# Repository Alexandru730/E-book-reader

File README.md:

# 📦 ESP32-C6 ePaper Project

Un proiect hardware ce integreaza un modul **ESP32-C6**, un **display e-Paper 7.5"**, alimentare prin **baterie Li-Ion** si conexiuni de testare prin **testpad-uri**. 

---

## 📊 Diagrama bloc

---

## 📦 BOM – Bill of Materials
| Componenta                 | Achizitie                                     | Datasheet                                   |
|---------------------------|-----------------------------------------------|---------------------------------------------|
| PFMF.050.1                | [Cumpara](https://ro.mouser.com/ProductDetail/Schurter/PFMF.050.2?qs=1auRipcfynCums5v1iucSA%3D%3D)                     | [Datasheet](https://ro.mouser.com/datasheet/2/358/typ_PFMF-1275918.pdf)                 |
| USB4110-GF-A              | [Cumpara](https://ro.mouser.com/ProductDetail/GCT/USB4110-GF-A?qs=KUoIvG%2F9IlYiZvIXQjyJeA%3D%3D)                     | [Datasheet](https://ro.mouser.com/datasheet/2/837/GCT_USB4110_Product_Drawing___20k_cycles-3455479.pdf)                 |
| USBLC6-2SC6Y              | [Cumpara](https://ro.mouser.com/ProductDetail/STMicroelectronics/USBLC6-2SC6Y?qs=gNDSiZmRJS%2FOgDexvXkdow%3D%3D)                     | [Datasheet](https://ro.mouser.com/datasheet/2/389/usblc6_2sc6y-1852505.pdf)                 |
| SD0805S020S1R0            | [Cumpara](https://ro.mouser.com/ProductDetail/KYOCERA-AVX/SD0805S020S1R0?qs=jCA%252BPfw4LHbpkAoSnwrdjw%3D%3D)                     | [Datasheet](https://ro.mouser.com/datasheet/2/40/schottky-3165252.pdf)                 |
| DMG2305UX-7               | [Cumpara](https://ro.mouser.com/ProductDetail/Diodes-Incorporated/DMG2305UX-7?qs=L1DZKBg7t5F%2FNBHrjfxC%252Bg%3D%3D)                     | [Datasheet](https://www.diodes.com/assets/Datasheets/DMG2305UX.pdf)                 |
| XC6220A331MR-G            | [Cumpara](https://ro.mouser.com/ProductDetail/Torex-Semiconductor/XC6220A331MR-G?qs=AsjdqWjXhJ8ZSWznL1J0gg%3D%3D)                     | [Datasheet](https://ro.mouser.com/datasheet/2/760/xc6220-3371556.pdf)                 |
| Condensator 100 uF TANT   | [Cumpara](https://ro.mouser.com/ProductDetail/KYOCERA-AVX/TAJW107M010RNJ?qs=Wtp%252Bf%2FAeVqIH8v1VxV%252B1Rg%3D%3D)                     | [Datasheet](https://ro.mouser.com/datasheet/2/40/TAJ-3165264.pdf)                 |
| 112A-TAAR-R03_ATTEND      | [Cumpara](https://www.digikey.ro/en/products/detail/attend-technology/112A-TAAR-R03/17633923)                     | [Datasheet](https://www.attend.com.tw/data/download/file/112A-TAAR-R03_Spec.pdf)                 |
| ESP32-C6-WROOM-1-N8       | [Cumpara](https://ro.mouser.com/ProductDetail/Espressif-Systems/ESP32-C6-WROOM-1-N8?qs=8Wlm6%252BaMh8ST02Gmwp74cw%3D%3D)                     | [Datasheet](https://ro.mouser.com/datasheet/2/891/Espressif_ESP32_C6_WROOM_1__Datasheet_V0_1_PRELIMI-3239987.pdf)                 |
| MCP73831                  | [Cumpara](https://ro.mouser.com/ProductDetail/Microchip-Technology/MCP73831T-2ACI-OT?qs=yUQqVecv4qvbBQBGbHx0Mw%3D%3D)                     | [Datasheet](https://ro.mouser.com/datasheet/2/268/MCP73831_Family_Data_Sheet_DS20001984H-3441711.pdf)                 |
| CHG_LED                   | [Cumpara](https://store.comet.srl.ro/Catalogue/Product/40478/)                     | [Datasheet](https://www.snapeda.com/parts/KP-1608SURCK/Kingbright/datasheet/)                 |
| SI1308EDL-T1-GE3          | [Cumpara](https://ro.mouser.com/ProductDetail/Vishay-Semiconductors/SI1308EDL-T1-GE3?qs=bX1%252BNvsK%2FBramh9tgpOaEw%3D%3D)                     | [Datasheet](https://www.vishay.com/doc?63399)                 |
| MBR0530                   | [Cumpara](https://ro.mouser.com/ProductDetail/Micro-Commercial-Components-MCC/MBR0530-T?qs=9VyI4qLX4NTSXkb9ynzJnA%3D%3D)                     | [Datasheet](https://ro.mouser.com/datasheet/2/258/mcc_mbr0520~mbr0560sod123-1179695.pdf)                 |
| Bobina                    | [Cumpara](https://ro.mouser.com/ProductDetail/Wurth-Elektronik/744043680?qs=PGXP4M47uW6VkZq%252BkzjrHA%3D%3D)                     | [Datasheet](https://www.we-online.com/components/products/datasheet/744043680.pdf)                 |
| FH34SRJ-24S-0.5SH_99_     | [Cumpara](https://ro.mouser.com/ProductDetail/Hirose-Connector/FH34SRJ-24S-0.5SH99?qs=vcbW%252B4%252BSTIpKBl5ap9J8Fw%3D%3D)                     | [Datasheet](https://ro.mouser.com/datasheet/2/185/FH34SRJ_24S_0_5SH_99__CL0580_1255_6_99_2DDrawing_0-1615044.pdf)                 |
| BME688                    | [Cumpara](https://ro.mouser.com/ProductDetail/Bosch-Sensortec/BME688?qs=IS%252B4QmGtzzqQoVDscqwx3A%3D%3D)                     | [Datasheet](https://ro.mouser.com/datasheet/2/783/bst_bme688_fl000-2307034.pdf)                 |
| BD5229G-TR                | [Cumpara](https://ro.mouser.com/ProductDetail/ROHM-Semiconductor/BD5229G-TR?qs=4kLU8WoGk0vvnhrrYwdszw%3D%3D)                     | [Datasheet](https://fscdn.rohm.com/en/products/databook/datasheet/ic/power/voltage_detector/bd52xxg-e.pdf)                 |
| Switch             | [Cumpara](https://ro.mouser.com/ProductDetail/CK/KMR221GULCLFS?qs=u2NJ%252B70r0goBXaNk7IrU0Q%3D%3D)                     | [Datasheet](https://www.ckswitches.com/media/1479/kmr2.pdf)                 |
| MAX17048G+T10             | [Cumpara](https://ro.mouser.com/ProductDetail/Analog-Devices-Maxim-Integrated/MAX17048G%2bT10?qs=D7PJwyCwLAoGnnn8jEPRBQ%3D%3D)                     | [Datasheet](https://ro.mouser.com/datasheet/2/609/MAX17048_MAX17049-3469099.pdf)                 |
| W25Q512JVEIQ              | [Cumpara](https://ro.mouser.com/ProductDetail/Winbond/W25Q512JVEIQ?qs=l7cgNqFNU1jw6svr3at6tA%3D%3D)                     | [Datasheet](https://ro.mouser.com/datasheet/2/949/Winbond_W25Q512JV_Datasheet-3240039.pdf)                 |
| PGB1010603MR              | [Cumpara](https://ro.mouser.com/ProductDetail/Littelfuse/PGB1010603MRHF?qs=KvZd0dN2Zg%2FuIq6icj%252BGKA%3D%3D)                     | [Datasheet](https://www.littelfuse.com/media?resourcetype=datasheets&itemid=8a337998-d54d-466b-be4e-dc5bcd1f9321&filename=littelfuse_pulseguard_pgb1_datasheet.pdf)                 |
| QWIIC_RIGHT_ANGLE         | [Cumpara](https://ro.mouser.com/ProductDetail/Analog-Devices-Maxim-Integrated/DS3231SN?qs=ffX8NcjNb2RmKAb9wAk9Ug%3D%3D)                    | [Datasheet](https://ro.mouser.com/datasheet/2/837/GCT_USB4110_Product_Drawing___20k_cycles-3455479.pdf)                 |
| DS3231SN#                 | [Cumpara](https://ro.mouser.com/ProductDetail/Analog-Devices-Maxim-Integrated/DS3231SN?qs=ffX8NcjNb2RmKAb9wAk9Ug%3D%3D)                     | [Datasheet](https://ro.mouser.com/datasheet/2/609/DS3231-3421123.pdf)                 |
| CPH3225A C10_SUPERCAP     | [Cumpara](https://ro.mouser.com/ProductDetail/Seiko-Semiconductors/CPH3225A?qs=3etwrb1wR%252BhUOph6lAO7eg%3D%3D)                     | [Datasheet](https://ro.mouser.com/datasheet/2/360/Seiko_Instruments_MicroBattery_E_20230330_2024Jan_-3561061.pdf)                 |
| Condensator 100nF         | [Cumpara](https://ro.mouser.com/ProductDetail/KYOCERA-AVX/06033G104ZAT2A?qs=NXubJDmysXJMPmHfVo6Z%252BA%3D%3D)                     | [Datasheet](https://ro.mouser.com/datasheet/2/40/KGM_Y5V-3223189.pdf)                 |
| Condensator 4.7uF         | [Cumpara](https://ro.mouser.com/ProductDetail/KYOCERA-AVX/0402ZD475MAT2A?qs=NBFAU1oqP4W4U2PCPHI0sg%3D%3D)                     | [Datasheet](https://ro.mouser.com/datasheet/2/40/cx5r_KGM-3223198.pdf)                 |
| Condensator 10uF          | [Cumpara](https://ro.mouser.com/ProductDetail/Samsung-Electro-Mechanics/CL10A106KQ8NNNL?qs=xZ%2FP%252Ba9zWqaes9JKSsob2Q%3D%3D)                     | [Datasheet](https://ro.mouser.com/datasheet/2/585/MLCC-1837944.pdf)                 |
| Condensator 1uF/50V       | [Cumpara](https://ro.mouser.com/ProductDetail/KYOCERA-AVX/06035D105MAT2A?qs=k4kUdCzLgS5%252BURKe1SOIeQ%3D%3D)                     | [Datasheet](https://ro.mouser.com/datasheet/2/40/cx5r_KGM-3223198.pdf)                 |
| Rezistenta 10K            | [Cumpara](https://ro.mouser.com/ProductDetail/Vishay-Beyschlag/MCS0402MD1002BE000?qs=17u8i%2FzlE8%2F9BrAaXkMk1w%3D%3D)                     | [Datasheet](https://www.vishay.com/doc?28952)                 |
| Rezistenta 200            | [Cumpara](https://ro.mouser.com/ProductDetail/Vishay-Beyschlag/MCS0402MD2000BE100?qs=3SvaY9RawMJNVte4F12%252BZQ%3D%3D)                     | [Datasheet](https://www.vishay.com/doc?28952)                 |
| Rezistenta 100K           | [Cumpara](https://ro.mouser.com/ProductDetail/Vishay-Beyschlag/MCT0603PD1003DP500?qs=5aG0NVq1C4wWAn8Ei3OpZA%3D%3D)                     | [Datasheet](https://www.vishay.com/doc?28916)                 |
| Rezistenta 2.2            | [Cumpara](https://ro.mouser.com/ProductDetail/SEI-Stackpole/RMCF0402FT2R20?qs=IPgv5n7u5QbBgyl0jwhwsA%3D%3D)                     | [Datasheet](https://ro.mouser.com/datasheet/2/385/SEI_RMCF_RMCP-3077565.pdf)                 |
| Rezistenta 5K1            | [Cumpara](https://www.venkel.com/part/TFCR0603-16W-K-5690FT)                     | [Datasheet](https://ro.mouser.com/datasheet/2/385/SEI_RMCF_RMCP-3077565.pdf)                 |
| Rezistenta 2K             | [Cumpara](https://ro.mouser.com/ProductDetail/Vishay-Beyschlag/MCS04020C2001FE000?qs=wTZ%2FFzl837YG0wIkZJJOwQ%3D%3D)                     | [Datasheet](https://www.vishay.com/doc?28705)                 |
| Rezistenta 0.47           | [Cumpara](https://ro.mouser.com/ProductDetail/SEI-Stackpole/CSR0402JKR470?qs=IPgv5n7u5QawIB6nBEt8wA%3D%3D)                     | [Datasheet](https://ro.mouser.com/datasheet/2/385/SEI_CSR_CSRN-3077593.pdf)                 |
| Rezistenta 15             | [Cumpara](https://ro.mouser.com/ProductDetail/YAGEO/RT0402FRE0715RL?qs=BXCcY9r%252B08DFFpLSkPOIqQ%3D%3D)                     | [Datasheet](https://ro.mouser.com/datasheet/2/447/PYu_RT_1_to_0_01_RoHS_L_15-3461507.pdf)                 |
                                                  |

---

## ⚙️ Functionalitate Hardware

- 🧠 **ESP32-C6**: procesor principal, WiFi si BLE
- 🖼️ **Display e-Paper 7.5”**: conectat prin interfata SPI
- 🔋 **Baterie Li-Ion 3.7V**: conectare directa la testpad-uri
- 🧪 **Testpad-uri**: pentru alimentare, masuratori si debugging
- 🧲 Toate GND-urile sunt conectate intr-un plan de masa dublu (top/bottom) cu **via stitching**

---

# Tabel Pini ESP32-C6 - Configuratie si Functii

| Nume            | GPIO / Pin       | Functie                              | Descriere                                                                 |
|-----------------|------------------|--------------------------------------|---------------------------------------------------------------------------|
| 3V3             | 3V3              | Sursa 3.3V                           | Asigura alimentarea necesara functionarii ESP32-C6 si componentelor logice |
| EN (Reset)      | EN               | Activare/Dezactivare microcontroler | Reset hardware prin semnal LOW                                            |
| USB_D-          | IO12             | Linie USB negativa                   | Parte din perechea diferentiala pentru USB 2.0                            |
| USB_D+          | IO13             | Linie USB pozitiva                   | Parte din perechea diferentiala pentru USB 2.0                            |
| Buton Boot      | IO9              | Mod bootloader                       | Se conecteaza la GND pentru a initia programarea                          |
| Buton Change    | IO15             | Mod operare                          | Comuta intre moduri definite in firmware                                  |
| TX (UART)       | GPIO16 (TXD0)    | UART TX                              | Transmitere date seriale                                                  |
| RX (UART)       | GPIO17 (RXD0)    | UART RX                              | Receptie date seriale                                                     |
| SCK (SPI)       | IO6              | SPI Clock                            | Ceas pentru comunicatia SPI                                               |
| MOSI (SPI)      | IO7              | SPI Master Out                       | Transmitere date SPI                                                      |
| MISO (SPI)      | IO2              | SPI Master In                        | Receptie date SPI                                                         |
| FLASH_CS        | IO11             | Chip Select NOR Flash                | Activeaza memoria flash                                                   |
| EPD_CS          | IO10             | Chip Select E-Paper                  | Activeaza ecranul E-Paper                                                 |
| EPD_DC          | IO5              | Comanda/Date E-Paper                 | Diferentiaza comenzi vs date pentru E-Paper                              |
| EPD_RST         | IO23             | Reset E-Paper                        | Reset hardware pentru E-Paper                                             |
| EPD_BUSY        | IO3              | Busy E-Paper                         | Semnalizeaza ca E-Paper este ocupat                                      |
| SDA (I2C)       | IO21             | I2C Data                             | Comunicatie cu RTC, BME688, etc.                                          |
| SCL (I2C)       | IO22             | I2C Clock                            | Ceas I2C                                                                  |
| SS_SD           | IO4              | Chip Select SD Card                  | Activeaza cardul SD                                                       |
| I2C_PW          | IO19             | Power control senzori I2C            | Activeaza/dezactiveaza alimentarea senzorilor I2C                         |
| EPD_3V3_C       | IO20             | Alimentare 3.3V E-Paper              | Sursa dedicata pentru E-Paper                                             |
| 32KHZ           | IO1              | Semnal 32kHz                         | Clock pentru RTC sau alte functii                                         |
| INT_RTC         | IO0              | Intrerupere RTC                      | Trezeste sistemul sau semnaleaza un eveniment RTC                         |
| RTC_RST         | IO18             | Reset RTC                            | Permite resetarea manuala a ceasului RTC                                  |

---

## 🖼️ Design Mecanic & 3D

- ✅ PCB proiectat si exportat 3D in Autodesk Fusion
- ✅ Model 3D complet pentru **baterie** si **display**, pe baza dimensiunilor din datasheet
- ✅ Integrare completa in **carcasa 3D** (asamblare in Fusion)
- ✅ Exploded view pentru randare si prezentare

---

## 🖼️ Randari

- ✅  
- ✅ 
- ✅ 

---
# Vizualizare 3D Autodesk

Model 3D interactiv găzduit pe Autodesk Viewer.

[🔗 Modelul direct in Autodesk Viewer](https://stud33517.autodesk360.com/shares/public/SH30dd5QT870c25f12fc75d2ac08da186a19).1

## Etape de implementare:
 - Am inceput cu asamblarea pieselor in schematic din biblioteca data, apoi cu trecerea la placa pcb, decuparea placii, masuratori luate pentru amplasarea corecta a pieselor si pentru integrarea usoara a placii in carcasa data.
 - A urmat amplasarea pieselor, am facut traseele de putere manual cu grosimea de 0.3mm, iar apoi pentru celelate trasee am folosit autoroute, cu grosimea de 0.16mm, un singur vias pe un traseu de putere am avut pentru ca nu am mai avut cum sa il leg pe layer-ul top.
 - Am facut planul de masa pe bottom si pe top, am folosit via stitching.
 - Iar apoi am trecut la pcb in 3d, am incarcat toate piesele in 3d si am trecut la masuratorile pentru baterie si ecran.
 - Bateria am facut-o simpla cu doua iesiri legate la doua testpaduri, vbat si gnd.
 - Display-ul l-am realizat dupa masuratorile date din datasheet, i-am facut si acel conector care intra in spatiul liber din placuta la connector display

# Erori
1. Am avut doua erori pe care le-am aprobat in pcb("Copper Width"), dar ele aveau grosimea buna.
2. Am gresit ceva si m-am intors la o varianta anterioara a pcb ului si dupa nu a mai fost sincronizat cu schematicul si nu mi-a mai mers randarea in 3d a placii si am luat totul de la inceput.
3. Mi s-a sters o componenta, mai exact cea de langa reset button, label-ul de RESET si am vazut abia la finalul proiectului, daca incercam sa o inlocuiesc cu ce trebuia mi se dadea totul peste cap si trebuia sa o iau de la capat, aveam niste erori care nu ma mai lasau sa dau push to 3d la pcb si nu se vedeau componentele in 3D, ceva warning uri in schematic, care ziceau de fire ca nu erau legate bine, sau ca o anumita componenta avea 3 iesiri, dar ea avea doar una.

## License

This project is licensed under the Apache License 2.0 - see the [LICENSE](LICENSE) file for details.

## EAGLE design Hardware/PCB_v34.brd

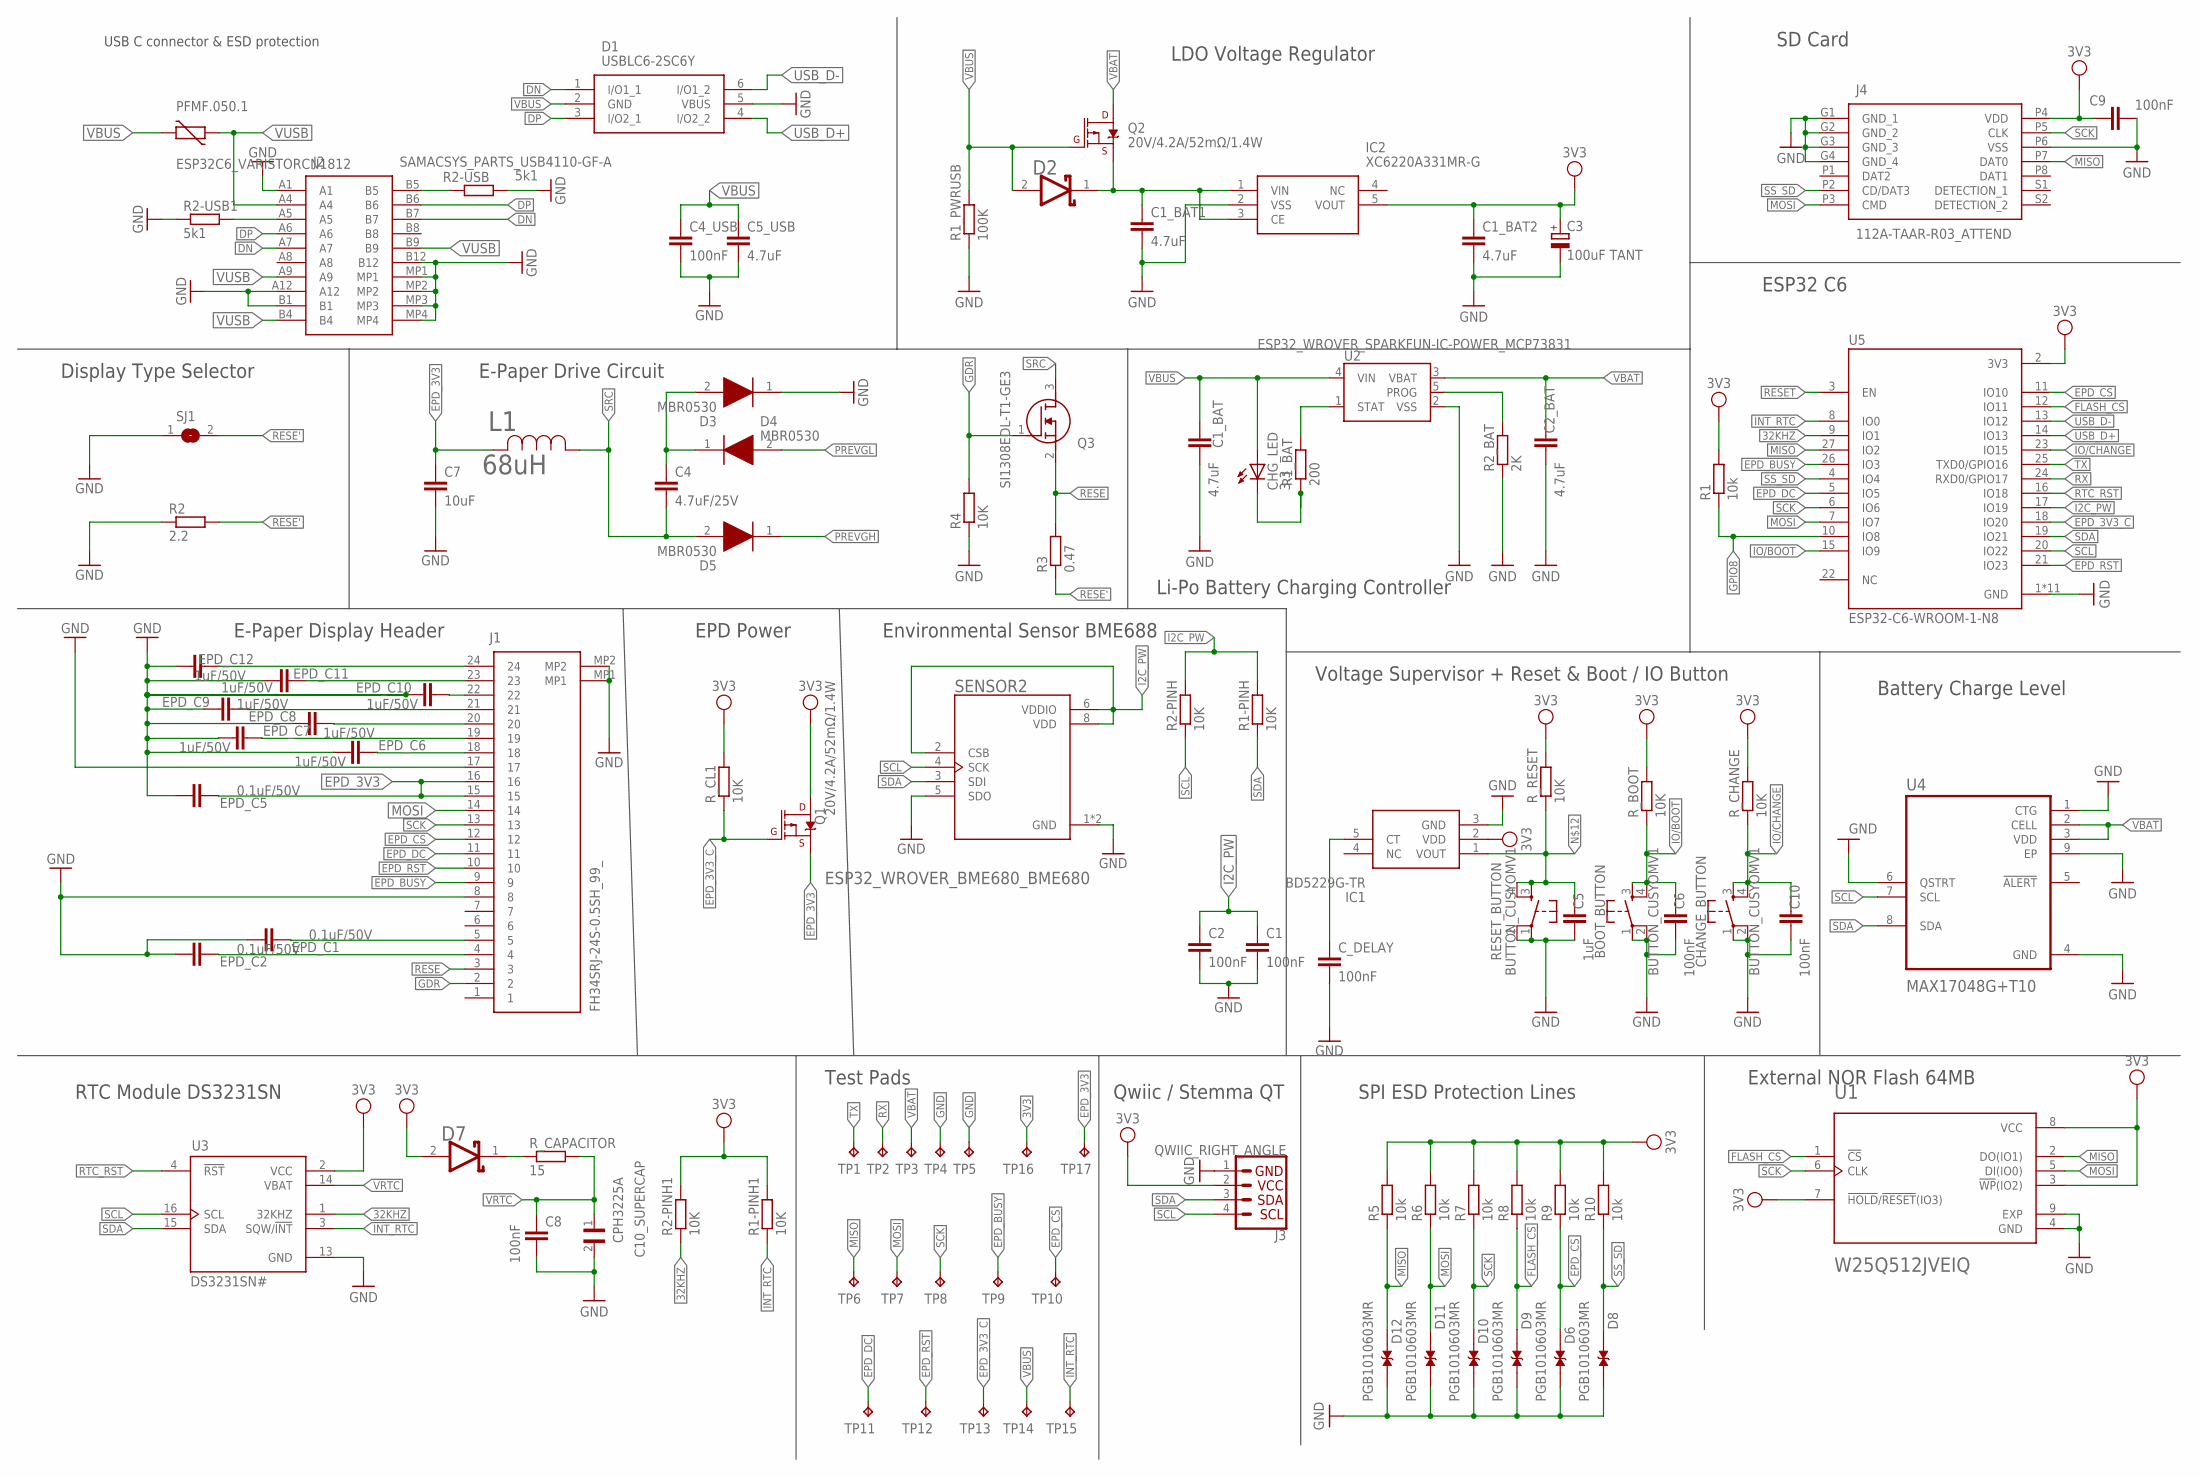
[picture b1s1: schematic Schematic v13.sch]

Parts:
BOOT_BUTTON: BUTTON_CUSYOMV1; MYBUTTON
C1, C2, C4_USB, C6, C8, C9, C10: 100nF; ESP32_WROVER_EAGLE-LTSPICE_C0402
C1_BAT, C2_BAT, C5_USB: 4.7uF; ESP32_WROVER_EAGLE-LTSPICE_C0402
C1_BAT1, C1_BAT2: 4.7uF; EAGLE-LTSPICE_C0402
C3: 100uF TANT; RCL_CT3528
C4: 4.7uF/25V; ESP32_WROVER_EAGLE-LTSPICE_C0402
C5: 1uF; ESP32_WROVER_EAGLE-LTSPICE_C0402
C7: 10uF; ESP32_WROVER_EAGLE-LTSPICE_C0402
C10_SUPERCAP: CPH3225A; CAPCP3225X100N
CHANGE_BUTTON: BUTTON_CUSYOMV1; MYBUTTON
CHG_LED: 3.3; ADAFRUIT_CHIP-LED0603
C_DELAY: 100nF; ESP32_WROVER_EAGLE-LTSPICE_C0402
D1: USBLC6-2SC6Y; SOT95P280X145-6N
D2, D7: ESP32_WROVER_AVX---SD0805S020S1R0_AVX_SD0805S020S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; ESP32_WROVER_AVX---SD0805S020S1R0_AVX_SD0805S020S1R0_0
D3, D4, D5: MBR0530; SOD3716X135N
D6, D8, D9, D10, D11, D12: PGB1010603MR; DIOC1608X36N
EPD_C1, EPD_C2, EPD_C5: 0.1uF/50V; ESP32_WROVER_EAGLE-LTSPICE_C0402
EPD_C6, EPD_C7, EPD_C8, EPD_C9, EPD_C10, EPD_C11, EPD_C12: 1uF/50V; ESP32_WROVER_EAGLE-LTSPICE_C0402
IC1: BD5229G-TR; SOT95P280X125-5N
IC2: XC6220A331MR-G; SOT95P280X120-5N
J1: FH34SRJ-24S-0.5SH_99_; FH34SRJ24S05SH99
J2: SAMACSYS_PARTS_USB4110-GF-A; SAMACSYS_PARTS_USB4110GFA
J3: QWIIC_RIGHT_ANGLE; JST04_1MM_RA
J4: 112A-TAAR-R03_ATTEND; 112ATAARR03ATTEND
L1: 68uH; IND_4828-WE-TPC_WRE
PFMF.050.1: ESP32C6_VARISTORCN1812; ESP32C6_VARISTOR_CT/CN1812
Q1, Q2: 20V/4.2A/52mΩ/1.4W; ESP32_WROVER_SPARKFUN-DISCRETESEMI_SOT23-3
Q3: SI1308EDL-T1-GE3; SOT65P210X110-3N
R1, R5, R6, R7, R8, R9, R10: 10k; ESP32_WROVER_EAGLE-LTSPICE_R0402
R1-PINH, R1-PINH1, R2-PINH, R2-PINH1, R4: 10K; ESP32_WROVER_EAGLE-LTSPICE_R0402
R1_BAT: 200; ESP32_WROVER_EAGLE-LTSPICE_R0402
R1_PWRUSB: 100K; ESP32_WROVER_EAGLE-LTSPICE_R0402
R2: 2.2; ESP32_WROVER_EAGLE-LTSPICE_R0402
R2-USB, R2-USB1: 5k1; ESP32_WROVER_EAGLE-LTSPICE_R0402
R2_BAT: 2K; ESP32_WROVER_EAGLE-LTSPICE_R0402
R3: 0.47; ESP32_WROVER_EAGLE-LTSPICE_R0402
RESET_BUTTON: BUTTON_CUSYOMV1; MYBUTTON
R_BOOT: 10K; ESP32_WROVER_EAGLE-LTSPICE_R0402
R_CAPACITOR: 15; ESP32_WROVER_EAGLE-LTSPICE_R0402
R_CHANGE: 10K; ESP32_WROVER_EAGLE-LTSPICE_R0402
R_CL1: 10K; ESP32_WROVER_EAGLE-LTSPICE_R0402
R_RESET: 10K; ESP32_WROVER_EAGLE-LTSPICE_R0402
SENSOR2: ESP32_WROVER_BME680_BME680; ESP32_WROVER_BME680_PSON80P300X300X100-8N
SJ1: SJ
TP1, TP2, TP3, TP4, TP5, TP6, TP7, TP8, TP9, TP10, TP11, TP12, TP13, TP14, TP15, TP16, TP17: TPTP20R; TP20R
U1: W25Q512JVEIQ; SON127P600X800X80-9N
U2: ESP32_WROVER_SPARKFUN-IC-POWER_MCP73831; ESP32_WROVER_SPARKFUN-IC-POWER_SOT23-5
U3: DS3231SN#; SOIC127P1032X265-16N
U4: MAX17048G+T10; SON50P200X200X80-9N
U5: ESP32-C6-WROOM-1-N8; XCVR_ESP32-C6-WROOM-1-N8

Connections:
3V3: C1_BAT2.1, C3.+, C9.1, D7.2 (ANODE), IC1.2 (VDD), IC2.5 (VOUT), J3.2, J4.P4 (VDD), Q1.3 (D), R1.2, R1-PINH1.2, R2-PINH1.2, R5.2, R6.2, R7.2, R8.2, R9.2, R10.2, R_BOOT.2, R_CHANGE.2, R_CL1.2, R_RESET.2, TP16.TP, U1.3 (!WP!(IO2)), U1.7 (!HOLD!/!RESET!(IO3)), U1.8 (VCC), U3.2 (VCC), U5.2 (3V3)
32KHZ: R2-PINH1.1, U3.1 (32KHZ), U5.9 (IO1)
DN: D1.1 (I/O1_1), J2.A7, J2.B7
DP: D1.3 (I/O2_1), J2.A6, J2.B6
EPD_3V3: C7.1, EPD_C5.2, J1.15, J1.16, L1.2, Q1.2 (S), TP17.TP
EPD_3V3_C: Q1.1 (G), R_CL1.1, TP13.TP, U5.18 (IO20)
EPD_BUSY: J1.9, TP9.TP, U5.26 (IO3)
EPD_CS: D6.2, J1.12, R9.1, TP10.TP, U5.11 (IO10)
EPD_DC: J1.11, TP11.TP, U5.5 (IO5)
EPD_RST: J1.10, TP12.TP, U5.21 (IO23)
FLASH_CS: D9.2, R8.1, U1.1 (!CS), U5.12 (IO11)
GDR: J1.2, Q3.1 (G), R4.2
GND: BOOT_BUTTON.1, BOOT_BUTTON.2, C1.2, C1_BAT.2, C1_BAT1.2, C1_BAT2.2, C2.2, C2_BAT.2, C3.-, C4_USB.2, C5.2, C5_USB.2, C6.2, C7.2, C8.2, C9.2, C10.2, C10_SUPERCAP.2, CHANGE_BUTTON.1, CHANGE_BUTTON.2, C_DELAY.2, D1.5 (VBUS), D3.1 (K), D6.1, D8.1, D9.1, D10.1, D11.1, D12.1, EPD_C1.1, EPD_C2.1, EPD_C5.1, EPD_C6.1, EPD_C7.1, EPD_C8.1, EPD_C9.1, EPD_C10.1, EPD_C11.1, EPD_C12.1, IC1.3 (GND), IC2.2 (VSS), J1.8, J1.17, J1.MP1, J1.MP2, J2.A1, J2.A12, J2.B1, J2.B12, J2.MP1, J2.MP2, J2.MP3, J2.MP4, J3.1, J4.G1 (GND_1), J4.G2 (GND_2), J4.G3 (GND_3), J4.G4 (GND_4), J4.P6 (VSS), R1_PWRUSB.1, R2.1, R2-USB.2, R2-USB1.1, R2_BAT.1, R4.1, RESET_BUTTON.1, RESET_BUTTON.2, SENSOR2.1 (GND), SENSOR2.5 (SDO), SENSOR2.7 (GND), SJ1.1, TP4.TP, TP5.TP, U1.4 (GND), U1.9 (EXP), U2.2 (VSS), U3.13 (GND), U4.1 (CTG), U4.4 (GND), U4.6 (QSTRT), U4.9 (EP), U5.1 (GND), U5.28 (GND), U5.29_1 (GND), U5.29_2 (GND), U5.29_3 (GND), U5.29_4 (GND), U5.29_5 (GND), U5.29_6 (GND), U5.29_7 (GND), U5.29_8 (GND), U5.29_9 (GND)
GPIO8: R1.1, U5.10 (IO8)
I2C_PW: C1.1, C2.1, R1-PINH.2, R2-PINH.2, SENSOR2.2 (CSB), SENSOR2.6 (VDDIO), SENSOR2.8 (VDD), U5.17 (IO19)
INT_RTC: R1-PINH1.1, TP15.TP, U3.3 (SQW/!INT), U5.8 (IO0)
IO/BOOT: BOOT_BUTTON.3, BOOT_BUTTON.4, C6.1, R_BOOT.1, U5.15 (IO9)
IO/CHANGE: C10.1, CHANGE_BUTTON.3, CHANGE_BUTTON.4, R_CHANGE.1, U5.23 (IO15)
MISO: D12.2, J4.P7 (DAT0), R5.1, TP6.TP, U1.2 (DO(IO1)), U5.27 (IO2)
MOSI: D11.2, J1.14, J4.P3 (CMD), R6.1, TP7.TP, U1.5 (DI(IO0)), U5.7 (IO7)
unnamed: J2.B5, R2-USB.1
unnamed: D7.1 (CATHODE), R_CAPACITOR.1
unnamed: J2.A5, R2-USB1.2
unnamed: EPD_C11.2, J1.23
unnamed: EPD_C10.2, J1.22
unnamed: EPD_C9.2, J1.21
unnamed: C4.1, D3.2 (A), D4.1 (K)
unnamed: EPD_C8.2, J1.20
unnamed: EPD_C7.2, J1.19
unnamed: EPD_C6.2, J1.18
unnamed: C_DELAY.1, IC1.5 (CT)
unnamed: R1_BAT.2, U2.1 (STAT)
unnamed: CHG_LED.C, R1_BAT.1
unnamed: C1_BAT1.1, D2.1 (CATHODE), IC2.1 (VIN), IC2.3 (CE), Q2.2 (S)
unnamed: R2_BAT.2, U2.5 (PROG)
unnamed: EPD_C1.2, J1.5
unnamed: EPD_C2.2, J1.4
unnamed: EPD_C12.2, J1.24
PREVGH: D5.1 (K)
PREVGL: D4.2 (A)
RESE: J1.3, Q3.2 (S), R3.2
RESE': R2.2, R3.1, SJ1.2
RTC_RST: U3.4 (!RST), U5.16 (IO18)
RX: TP2.TP, U5.24 (RXD0/GPIO17)
SCK: D10.2, J1.13, J4.P5 (CLK), R7.1, TP8.TP, U1.6 (CLK), U5.6 (IO6)
SCL: J3.4, R2-PINH.1, SENSOR2.4 (SCK), U3.16 (SCL), U4.7 (SCL), U5.20 (IO22)
SDA: J3.3, R1-PINH.1, SENSOR2.3 (SDI), U3.15 (SDA), U4.8 (SDA), U5.19 (IO21)
SRC: C4.2, D5.2 (A), L1.1, Q3.3 (D)
SS_SD: D8.2, J4.P2 (CD/DAT3), R10.1, U5.4 (IO4)
TX: TP1.TP, U5.25 (TXD0/GPIO16)
USB_D+: D1.4 (I/O2_2), U5.14 (IO13)
USB_D-: D1.6 (I/O1_2), U5.13 (IO12)
VBAT: C2_BAT.1, Q2.3 (D), TP3.TP, U2.3 (VBAT), U4.2 (CELL), U4.3 (VDD)
VBUS: C1_BAT.1, C4_USB.1, C5_USB.1, CHG_LED.A, D1.2 (GND), D2.2 (ANODE), PFMF.050.1.2, Q2.1 (G), R1_PWRUSB.2, TP14.TP, U2.4 (VIN)
VRTC: C8.1, C10_SUPERCAP.1, R_CAPACITOR.2, U3.14 (VBAT)
VUSB: J2.A4, J2.A9, J2.B4, J2.B9, PFMF.050.1.1

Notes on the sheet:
USB C connector & ESD protection
SD Card
ESP32 C6
LDO Voltage Regulator
Display Type Selector
E-Paper Drive Circuit
E-Paper Display Header
EPD Power
Environmental Sensor BME688
Voltage Supervisor + Reset & Boot / IO Button
Battery Charge Level
External NOR Flash 64MB
SPI ESD Protection Lines
Qwiic / Stemma QT
Test Pads
RTC Module DS3231SN
Li-Po Battery Charging Controller

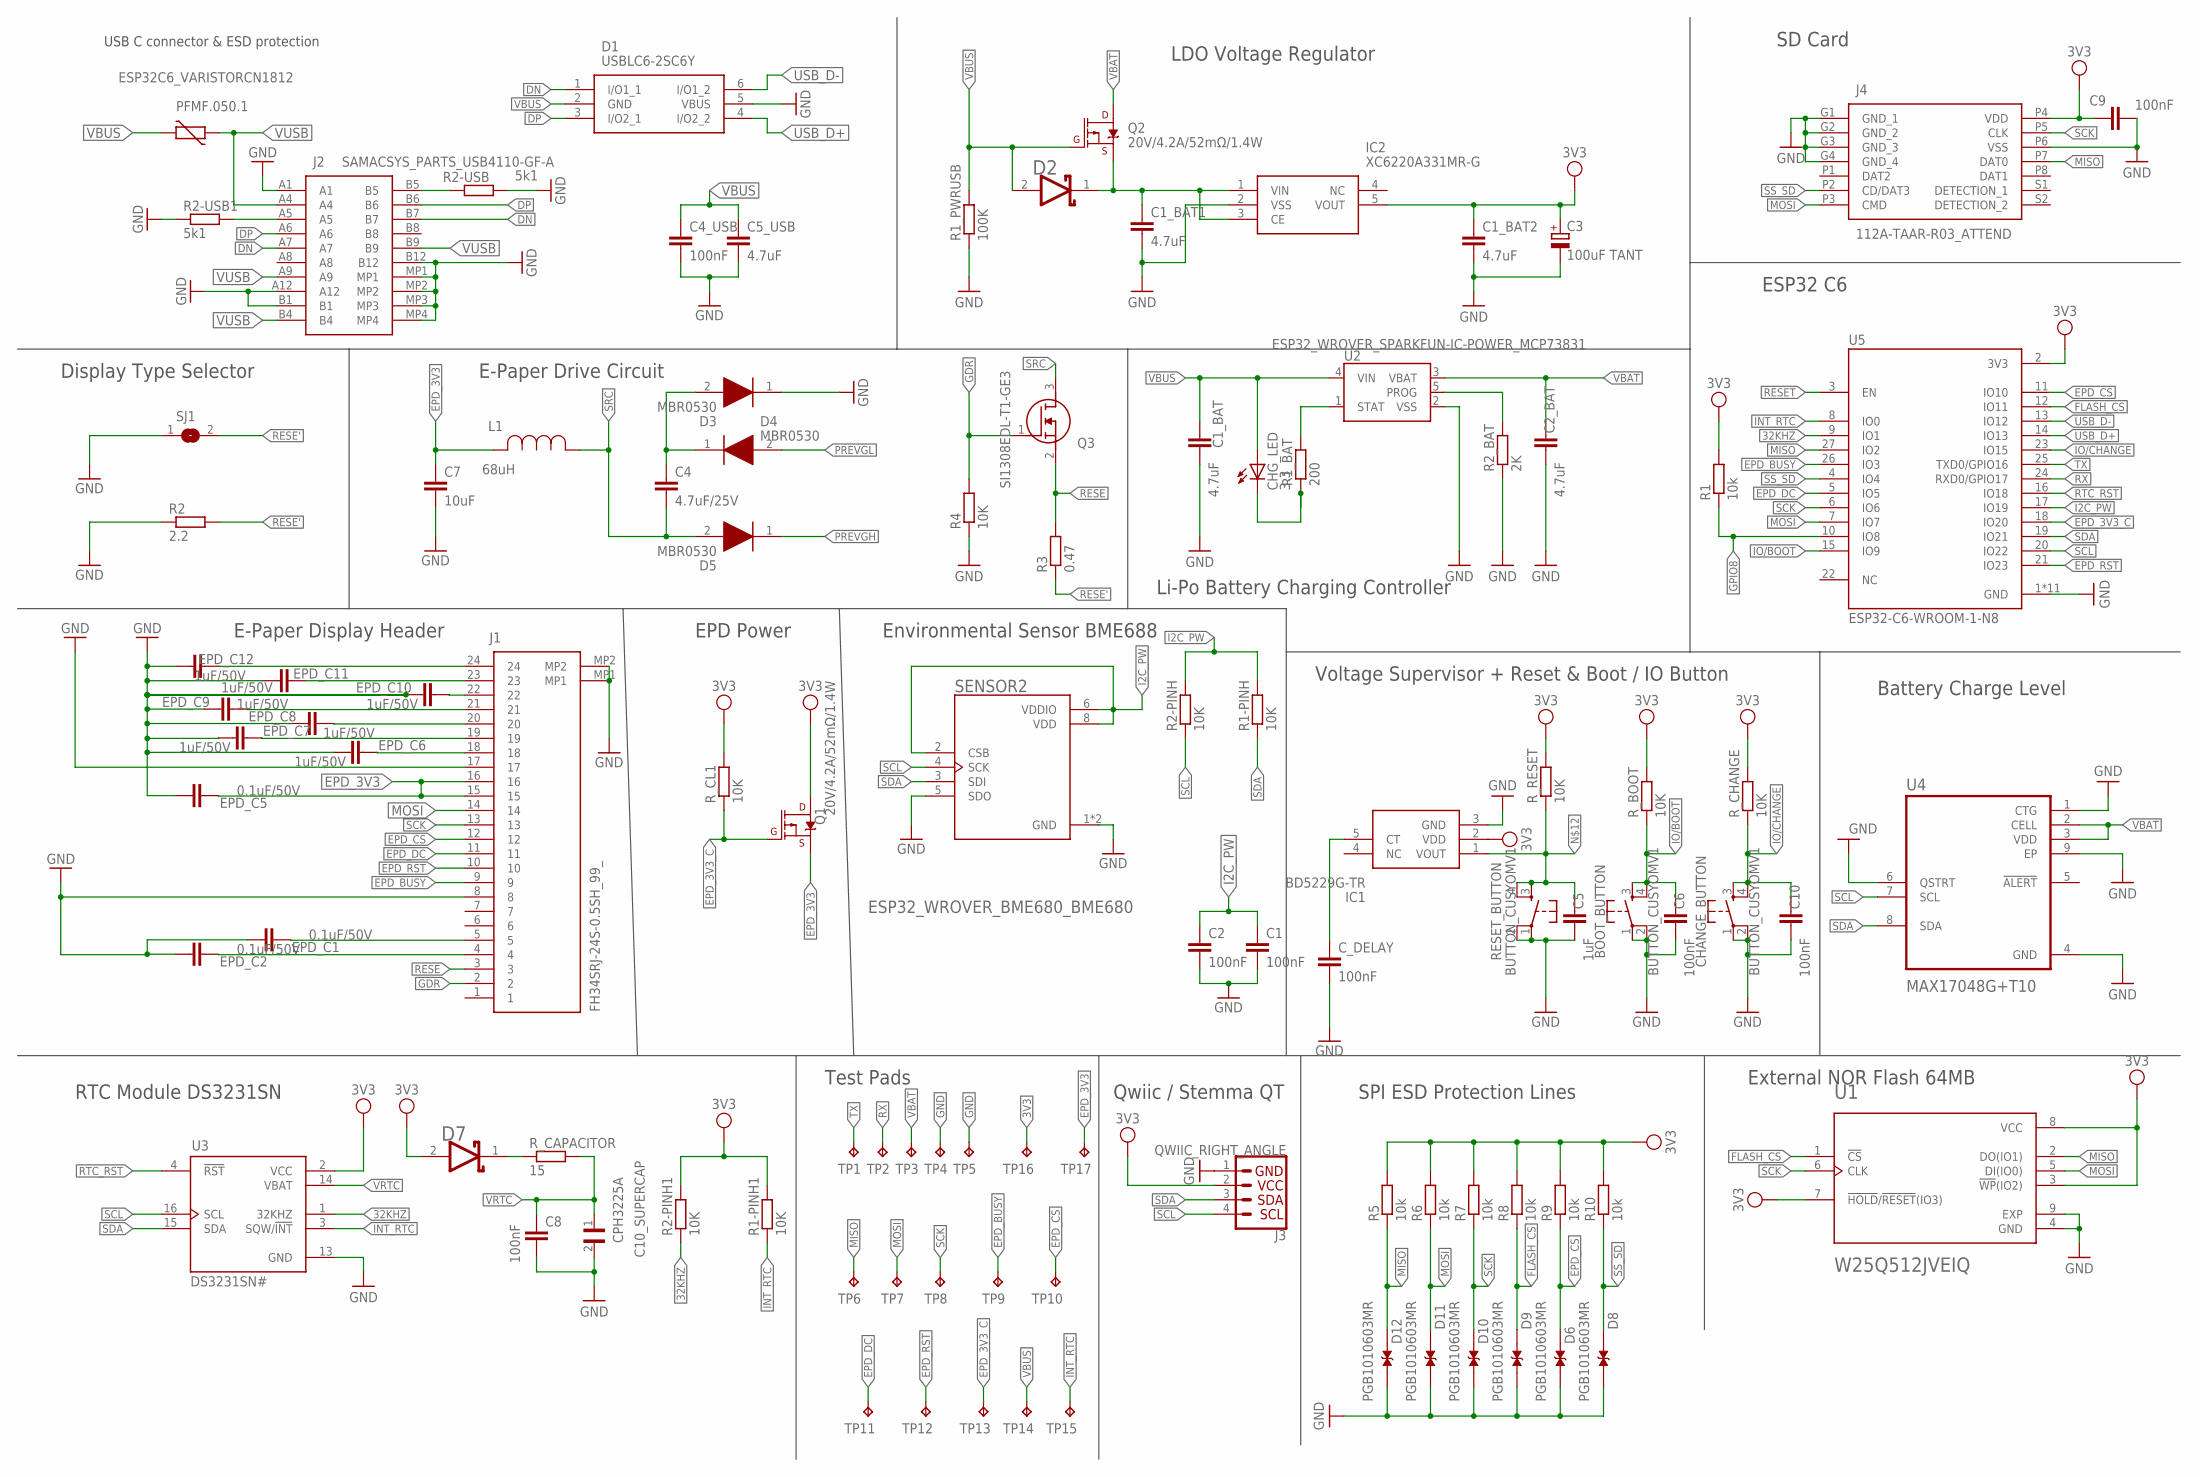
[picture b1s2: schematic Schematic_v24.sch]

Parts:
BOOT_BUTTON: BUTTON_CUSYOMV1; MYBUTTON
C1, C2, C4_USB, C6, C8, C9, C10: 100nF; ESP32_WROVER_EAGLE-LTSPICE_C0402
C1_BAT, C2_BAT, C5_USB: 4.7uF; ESP32_WROVER_EAGLE-LTSPICE_C0402
C1_BAT1, C1_BAT2: 4.7uF; EAGLE-LTSPICE_C0402
C3: 100uF TANT; RCL_CT3528
C4: 4.7uF/25V; ESP32_WROVER_EAGLE-LTSPICE_C0402
C5: 1uF; ESP32_WROVER_EAGLE-LTSPICE_C0402
C7: 10uF; ESP32_WROVER_EAGLE-LTSPICE_C0402
C10_SUPERCAP: CPH3225A; CAPCP3225X100N
CHANGE_BUTTON: BUTTON_CUSYOMV1; MYBUTTON
CHG_LED: 3.3; ADAFRUIT_CHIP-LED0603
C_DELAY: 100nF; ESP32_WROVER_EAGLE-LTSPICE_C0402
D1: USBLC6-2SC6Y; SOT95P280X145-6N
D2, D7: ESP32_WROVER_AVX---SD0805S020S1R0_AVX_SD0805S020S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; ESP32_WROVER_AVX---SD0805S020S1R0_AVX_SD0805S020S1R0_0
D3, D4, D5: MBR0530; SOD3716X135N
D6, D8, D9, D10, D11, D12: PGB1010603MR; DIOC1608X36N
EPD_C1, EPD_C2, EPD_C5: 0.1uF/50V; ESP32_WROVER_EAGLE-LTSPICE_C0402
EPD_C6, EPD_C7, EPD_C8, EPD_C9, EPD_C10, EPD_C11, EPD_C12: 1uF/50V; ESP32_WROVER_EAGLE-LTSPICE_C0402
IC1: BD5229G-TR; SOT95P280X125-5N
IC2: XC6220A331MR-G; SOT95P280X120-5N
J1: FH34SRJ-24S-0.5SH_99_; FH34SRJ24S05SH99
J2: SAMACSYS_PARTS_USB4110-GF-A; SAMACSYS_PARTS_USB4110GFA
J3: QWIIC_RIGHT_ANGLE; JST04_1MM_RA
J4: 112A-TAAR-R03_ATTEND; 112ATAARR03ATTEND
L1: 68uH; IND_4828-WE-TPC_WRE
PFMF.050.1: ESP32C6_VARISTORCN1812; ESP32C6_VARISTOR_CT/CN1812
Q1, Q2: 20V/4.2A/52mΩ/1.4W; ESP32_WROVER_SPARKFUN-DISCRETESEMI_SOT23-3
Q3: SI1308EDL-T1-GE3; SOT65P210X110-3N
R1, R5, R6, R7, R8, R9, R10: 10k; ESP32_WROVER_EAGLE-LTSPICE_R0402
R1-PINH, R1-PINH1, R2-PINH, R2-PINH1, R4: 10K; ESP32_WROVER_EAGLE-LTSPICE_R0402
R1_BAT: 200; ESP32_WROVER_EAGLE-LTSPICE_R0402
R1_PWRUSB: 100K; ESP32_WROVER_EAGLE-LTSPICE_R0402
R2: 2.2; ESP32_WROVER_EAGLE-LTSPICE_R0402
R2-USB, R2-USB1: 5k1; ESP32_WROVER_EAGLE-LTSPICE_R0402
R2_BAT: 2K; ESP32_WROVER_EAGLE-LTSPICE_R0402
R3: 0.47; ESP32_WROVER_EAGLE-LTSPICE_R0402
RESET_BUTTON: BUTTON_CUSYOMV1; MYBUTTON
R_BOOT: 10K; ESP32_WROVER_EAGLE-LTSPICE_R0402
R_CAPACITOR: 15; ESP32_WROVER_EAGLE-LTSPICE_R0402
R_CHANGE: 10K; ESP32_WROVER_EAGLE-LTSPICE_R0402
R_CL1: 10K; ESP32_WROVER_EAGLE-LTSPICE_R0402
R_RESET: 10K; ESP32_WROVER_EAGLE-LTSPICE_R0402
SENSOR2: ESP32_WROVER_BME680_BME680; ESP32_WROVER_BME680_PSON80P300X300X100-8N
SJ1: SJ
TP1, TP2, TP3, TP4, TP5, TP6, TP7, TP8, TP9, TP10, TP11, TP12, TP13, TP14, TP15, TP16, TP17: TPTP20R; TP20R
U1: W25Q512JVEIQ; SON127P600X800X80-9N
U2: ESP32_WROVER_SPARKFUN-IC-POWER_MCP73831; ESP32_WROVER_SPARKFUN-IC-POWER_SOT23-5
U3: DS3231SN#; SOIC127P1032X265-16N
U4: MAX17048G+T10; SON50P200X200X80-9N
U5: ESP32-C6-WROOM-1-N8; XCVR_ESP32-C6-WROOM-1-N8

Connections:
3V3: C1_BAT2.1, C3.+, C9.1, D7.2 (ANODE), IC1.2 (VDD), IC2.5 (VOUT), J3.2, J4.P4 (VDD), Q1.3 (D), R1.2, R1-PINH1.2, R2-PINH1.2, R5.2, R6.2, R7.2, R8.2, R9.2, R10.2, R_BOOT.2, R_CHANGE.2, R_CL1.2, R_RESET.2, TP16.TP, U1.3 (!WP!(IO2)), U1.7 (!HOLD!/!RESET!(IO3)), U1.8 (VCC), U3.2 (VCC), U5.2 (3V3)
32KHZ: R2-PINH1.1, U3.1 (32KHZ), U5.9 (IO1)
DN: D1.1 (I/O1_1), J2.A7, J2.B7
DP: D1.3 (I/O2_1), J2.A6, J2.B6
EPD_3V3: C7.1, EPD_C5.2, J1.15, J1.16, L1.2, Q1.2 (S), TP17.TP
EPD_3V3_C: Q1.1 (G), R_CL1.1, TP13.TP, U5.18 (IO20)
EPD_BUSY: J1.9, TP9.TP, U5.26 (IO3)
EPD_CS: D6.2, J1.12, R9.1, TP10.TP, U5.11 (IO10)
EPD_DC: J1.11, TP11.TP, U5.5 (IO5)
EPD_RST: J1.10, TP12.TP, U5.21 (IO23)
FLASH_CS: D9.2, R8.1, U1.1 (!CS), U5.12 (IO11)
GDR: J1.2, Q3.1 (G), R4.2
GND: BOOT_BUTTON.1, BOOT_BUTTON.2, C1.2, C1_BAT.2, C1_BAT1.2, C1_BAT2.2, C2.2, C2_BAT.2, C3.-, C4_USB.2, C5.2, C5_USB.2, C6.2, C7.2, C8.2, C9.2, C10.2, C10_SUPERCAP.2, CHANGE_BUTTON.1, CHANGE_BUTTON.2, C_DELAY.2, D1.5 (VBUS), D3.1 (K), D6.1, D8.1, D9.1, D10.1, D11.1, D12.1, EPD_C1.1, EPD_C2.1, EPD_C5.1, EPD_C6.1, EPD_C7.1, EPD_C8.1, EPD_C9.1, EPD_C10.1, EPD_C11.1, EPD_C12.1, IC1.3 (GND), IC2.2 (VSS), J1.8, J1.17, J1.MP1, J1.MP2, J2.A1, J2.A12, J2.B1, J2.B12, J2.MP1, J2.MP2, J2.MP3, J2.MP4, J3.1, J4.G1 (GND_1), J4.G2 (GND_2), J4.G3 (GND_3), J4.G4 (GND_4), J4.P6 (VSS), R1_PWRUSB.1, R2.1, R2-USB.2, R2-USB1.1, R2_BAT.1, R4.1, RESET_BUTTON.1, RESET_BUTTON.2, SENSOR2.1 (GND), SENSOR2.5 (SDO), SENSOR2.7 (GND), SJ1.1, TP4.TP, TP5.TP, U1.4 (GND), U1.9 (EXP), U2.2 (VSS), U3.13 (GND), U4.1 (CTG), U4.4 (GND), U4.6 (QSTRT), U4.9 (EP), U5.1 (GND), U5.28 (GND), U5.29_1 (GND), U5.29_2 (GND), U5.29_3 (GND), U5.29_4 (GND), U5.29_5 (GND), U5.29_6 (GND), U5.29_7 (GND), U5.29_8 (GND), U5.29_9 (GND)
GPIO8: R1.1, U5.10 (IO8)
I2C_PW: C1.1, C2.1, R1-PINH.2, R2-PINH.2, SENSOR2.2 (CSB), SENSOR2.6 (VDDIO), SENSOR2.8 (VDD), U5.17 (IO19)
INT_RTC: R1-PINH1.1, TP15.TP, U3.3 (SQW/!INT), U5.8 (IO0)
IO/BOOT: BOOT_BUTTON.3, BOOT_BUTTON.4, C6.1, R_BOOT.1, U5.15 (IO9)
IO/CHANGE: C10.1, CHANGE_BUTTON.3, CHANGE_BUTTON.4, R_CHANGE.1, U5.23 (IO15)
MISO: D12.2, J4.P7 (DAT0), R5.1, TP6.TP, U1.2 (DO(IO1)), U5.27 (IO2)
MOSI: D11.2, J1.14, J4.P3 (CMD), R6.1, TP7.TP, U1.5 (DI(IO0)), U5.7 (IO7)
unnamed: J2.B5, R2-USB.1
unnamed: D7.1 (CATHODE), R_CAPACITOR.1
unnamed: J2.A5, R2-USB1.2
unnamed: EPD_C11.2, J1.23
unnamed: EPD_C10.2, J1.22
unnamed: EPD_C9.2, J1.21
unnamed: C4.1, D3.2 (A), D4.1 (K)
unnamed: EPD_C8.2, J1.20
unnamed: EPD_C7.2, J1.19
unnamed: EPD_C6.2, J1.18
unnamed: C_DELAY.1, IC1.5 (CT)
unnamed: R1_BAT.2, U2.1 (STAT)
unnamed: CHG_LED.C, R1_BAT.1
unnamed: C1_BAT1.1, D2.1 (CATHODE), IC2.1 (VIN), IC2.3 (CE), Q2.2 (S)
unnamed: R2_BAT.2, U2.5 (PROG)
unnamed: EPD_C1.2, J1.5
unnamed: EPD_C2.2, J1.4
unnamed: EPD_C12.2, J1.24
PREVGH: D5.1 (K)
PREVGL: D4.2 (A)
RESE: J1.3, Q3.2 (S), R3.2
RESE': R2.2, R3.1, SJ1.2
RTC_RST: U3.4 (!RST), U5.16 (IO18)
RX: TP2.TP, U5.24 (RXD0/GPIO17)
SCK: D10.2, J1.13, J4.P5 (CLK), R7.1, TP8.TP, U1.6 (CLK), U5.6 (IO6)
SCL: J3.4, R2-PINH.1, SENSOR2.4 (SCK), U3.16 (SCL), U4.7 (SCL), U5.20 (IO22)
SDA: J3.3, R1-PINH.1, SENSOR2.3 (SDI), U3.15 (SDA), U4.8 (SDA), U5.19 (IO21)
SRC: C4.2, D5.2 (A), L1.1, Q3.3 (D)
SS_SD: D8.2, J4.P2 (CD/DAT3), R10.1, U5.4 (IO4)
TX: TP1.TP, U5.25 (TXD0/GPIO16)
USB_D+: D1.4 (I/O2_2), U5.14 (IO13)
USB_D-: D1.6 (I/O1_2), U5.13 (IO12)
VBAT: C2_BAT.1, Q2.3 (D), TP3.TP, U2.3 (VBAT), U4.2 (CELL), U4.3 (VDD)
VBUS: C1_BAT.1, C4_USB.1, C5_USB.1, CHG_LED.A, D1.2 (GND), D2.2 (ANODE), PFMF.050.1.2, Q2.1 (G), R1_PWRUSB.2, TP14.TP, U2.4 (VIN)
VRTC: C8.1, C10_SUPERCAP.1, R_CAPACITOR.2, U3.14 (VBAT)
VUSB: J2.A4, J2.A9, J2.B4, J2.B9, PFMF.050.1.1

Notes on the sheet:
USB C connector & ESD protection
SD Card
ESP32 C6
LDO Voltage Regulator
Display Type Selector
E-Paper Drive Circuit
E-Paper Display Header
EPD Power
Environmental Sensor BME688
Voltage Supervisor + Reset & Boot / IO Button
Battery Charge Level
External NOR Flash 64MB
SPI ESD Protection Lines
Qwiic / Stemma QT
Test Pads
RTC Module DS3231SN
Li-Po Battery Charging Controller

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
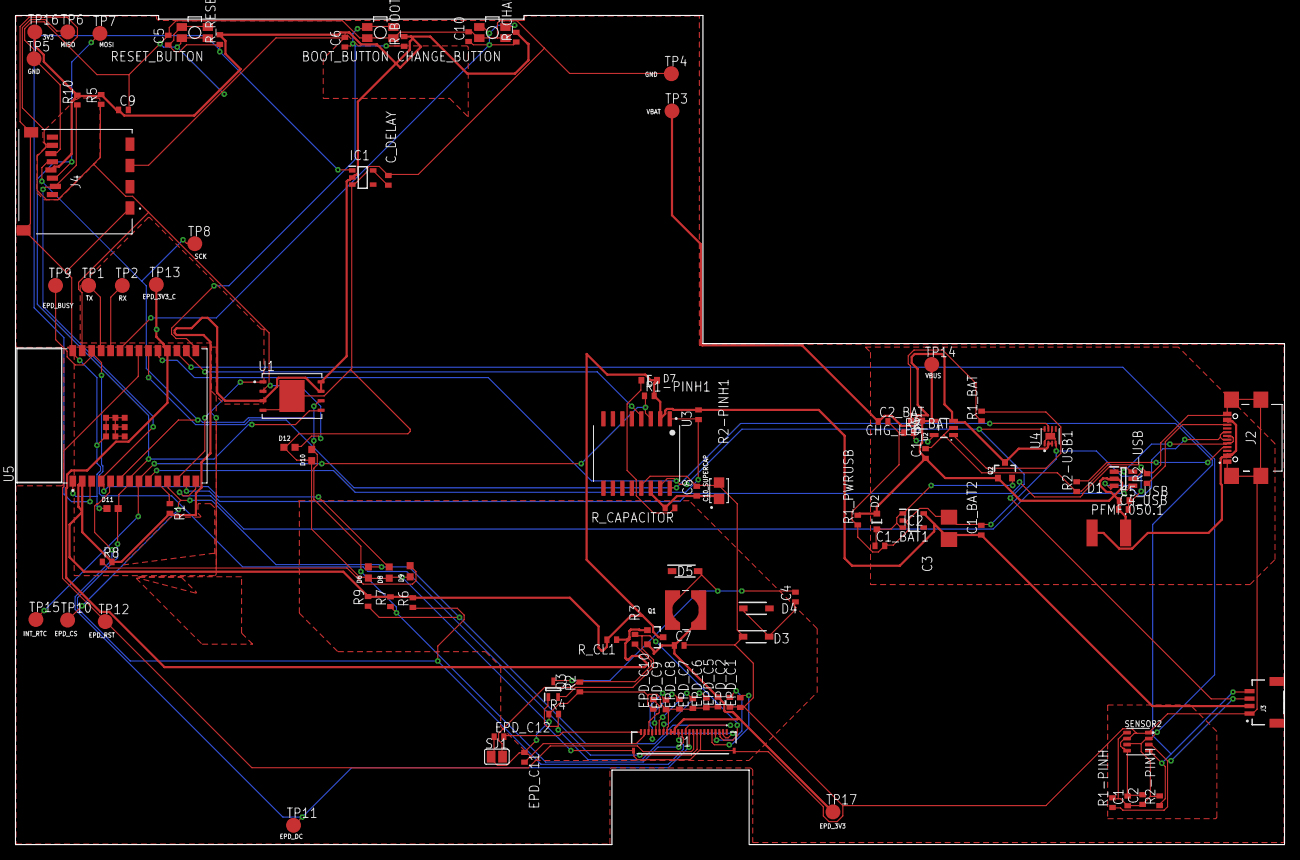
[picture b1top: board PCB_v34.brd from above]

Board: 2 copper layers, 170.2 x 111.2 mm, 103 parts (0 on the bottom side), 55 nets.

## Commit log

2025-04-06 Create LICENSE
2025-04-06 Update LICENSE

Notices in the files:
README.md:
License:
This project is licensed under the Apache License 2.0 - see the [LICENSE](LICENSE) file for details.
parts and their libraries:
COPYRIGHT: Copyright (C) 2024 Ultra Librarian. All rights reserved.
